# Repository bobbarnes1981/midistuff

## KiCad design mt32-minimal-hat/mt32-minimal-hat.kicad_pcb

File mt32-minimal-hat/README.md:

# mt32 minimal hat

https://github.com/raspberrypi/hats/blob/master/uhat-board-mechanical.pdf

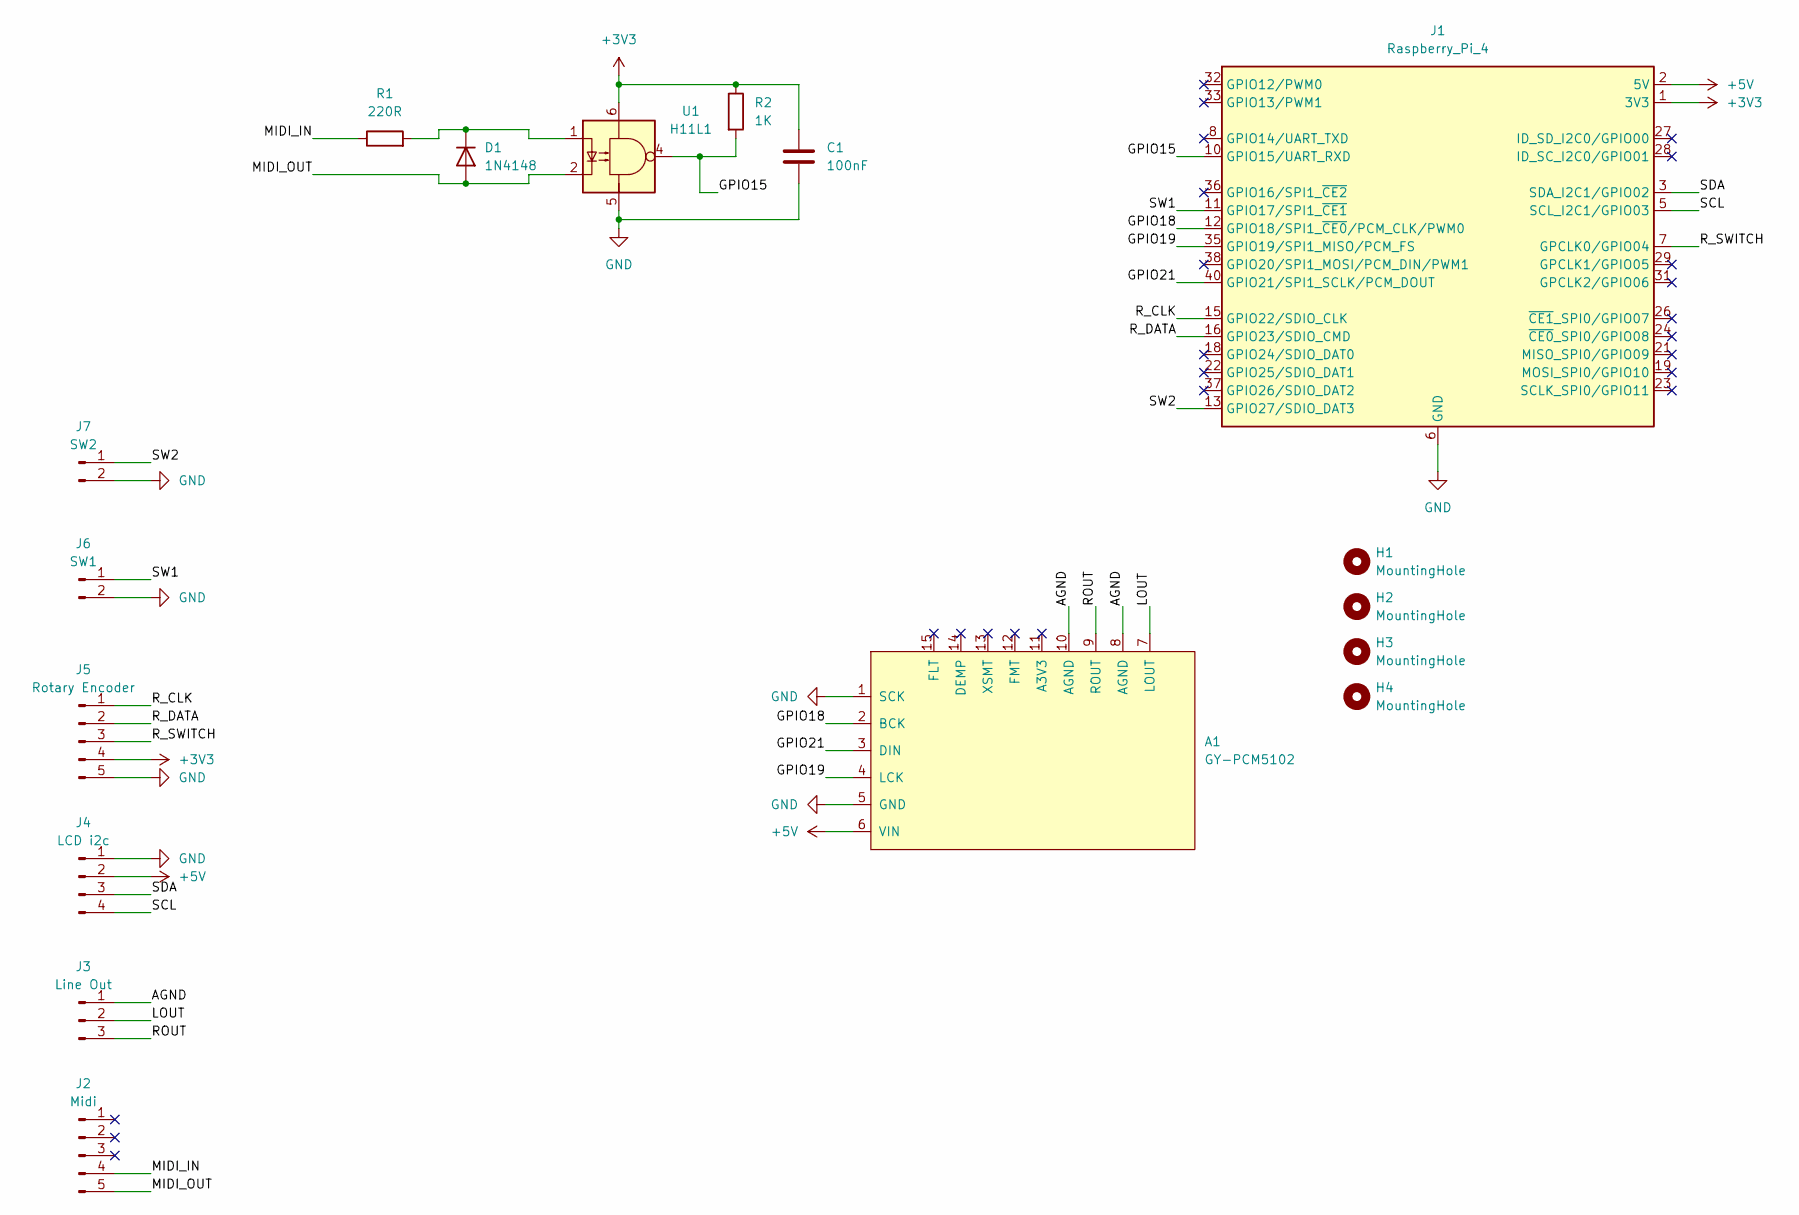
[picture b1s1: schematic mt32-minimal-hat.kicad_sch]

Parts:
A1: GY-PCM5102
C1: 100nF; C_Disc_D5.0mm_W2.5mm_P5.00mm
D1: 1N4148; D_DO-35_SOD27_P7.62mm_Horizontal
H1, H2, H3, H4: MountingHole; MountingHole_2.7mm_M2.5
J1: Raspberry_Pi_4; PinSocket_2x20_P2.54mm_Vertical
J2: Midi; PinHeader_1x05_P2.54mm_Vertical
J3: Line Out; PinHeader_1x03_P2.54mm_Vertical
J4: LCD i2c; PinHeader_1x04_P2.54mm_Vertical
J5: Rotary Encoder; PinHeader_1x05_P2.54mm_Vertical
J6: SW1; PinHeader_1x02_P2.54mm_Vertical
J7: SW2; PinHeader_1x02_P2.54mm_Vertical
R1: 220R; R_Axial_DIN0207_L6.3mm_D2.5mm_P10.16mm_Horizontal
R2: 1K; R_Axial_DIN0207_L6.3mm_D2.5mm_P10.16mm_Horizontal
U1: H11L1; DIP-6_W7.62mm_Socket_LongPads

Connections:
+3V3: C1.1, J1.1 (3V3), J1.17 (3V3), J5.4, R2.1, U1.6
+5V: A1.6 (VIN), J1.2 (5V), J1.4 (5V), J4.2
/AGND: A1.8 (AGND), A1.10 (AGND), J3.1
/GPIO15: J1.10 (GPIO15/UART_RXD), R2.2, U1.4
/GPIO18: A1.2 (BCK), J1.12 (GPIO18/SPI1_~CE0/PCM_CLK/PWM0)
/GPIO19: A1.4 (LCK), J1.35 (GPIO19/SPI1_MISO/PCM_FS)
/GPIO21: A1.3 (DIN), J1.40 (GPIO21/SPI1_SCLK/PCM_DOUT)
/LOUT: A1.7 (LOUT), J3.2
/MIDI_IN: J2.4, R1.1
/MIDI_OUT: D1.2 (A), J2.5, U1.2
/ROUT: A1.9 (ROUT), J3.3
/R_CLK: J1.15 (GPIO22/SDIO_CLK), J5.1
/R_DATA: J1.16 (GPIO23/SDIO_CMD), J5.2
/R_SWITCH: J1.7 (GPCLK0/GPIO04), J5.3
/SCL: J1.5 (SCL_I2C1/GPIO03), J4.4
/SDA: J1.3 (SDA_I2C1/GPIO02), J4.3
/SW1: J1.11 (GPIO17/SPI1_~CE1), J6.1
/SW2: J1.13 (GPIO27/SDIO_DAT3), J7.1
GND: A1.1 (SCK), A1.5 (GND), C1.2, J1.6 (GND), J1.9 (GND), J1.14 (GND), J1.20 (GND), J1.25 (GND), J1.30 (GND), J1.34 (GND), J1.39 (GND), J4.1, J5.5, J6.2, J7.2, U1.5
unnamed: D1.1 (K), R1.2, U1.1

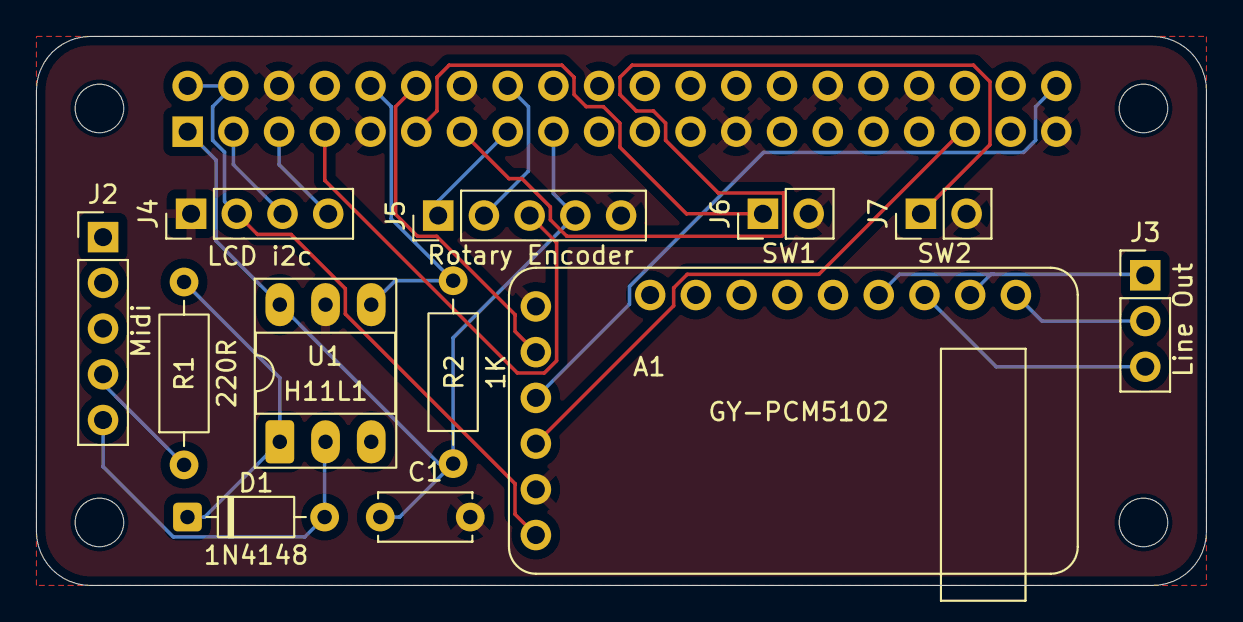
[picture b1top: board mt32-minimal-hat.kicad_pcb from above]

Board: 2 copper layers, 65.0 x 30.5 mm, 17 parts (1 on the bottom side), 20 nets.

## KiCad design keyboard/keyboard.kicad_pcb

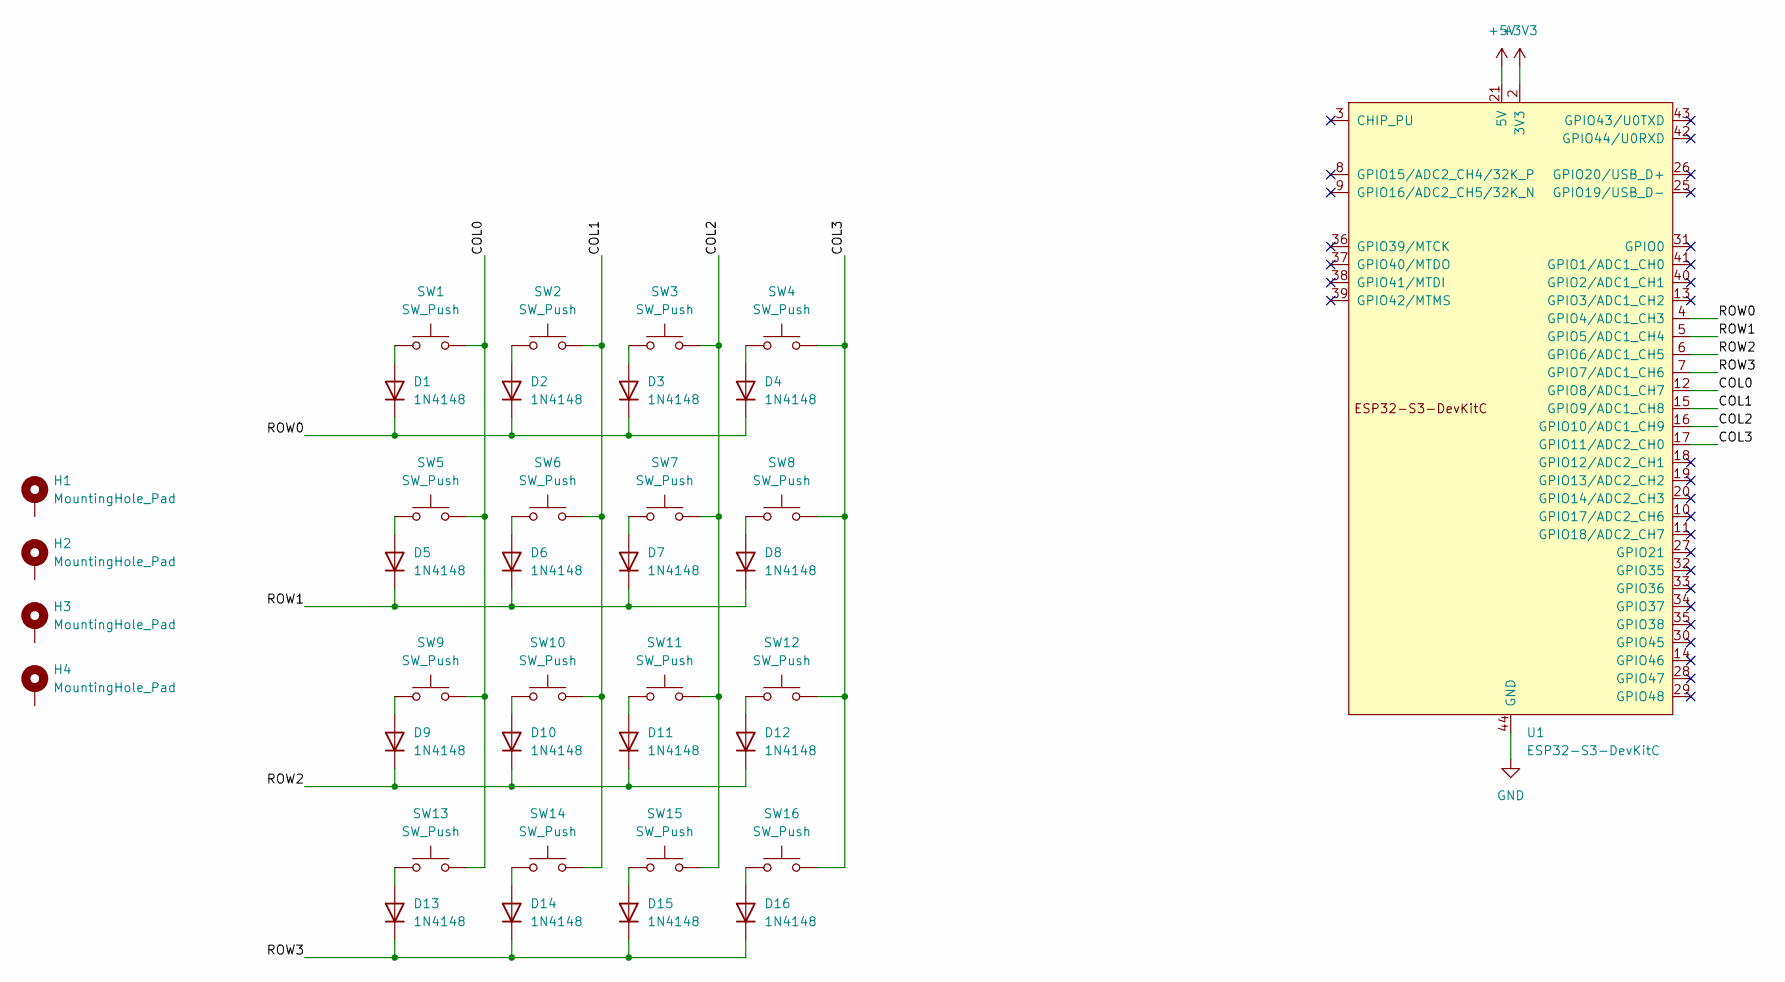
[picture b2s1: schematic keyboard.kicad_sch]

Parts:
D1, D2, D3, D4, D5, D6, D7, D8, D9, D10, D11, D12, D13, D14, D15, D16: 1N4148; D_DO-35_SOD27_P7.62mm_Horizontal
H1, H2, H3, H4: MountingHole_Pad; MountingHole_3.2mm_M3_Pad
SW1, SW2, SW3, SW4, SW5, SW6, SW7, SW8, SW9, SW10, SW11, SW12, SW13, SW14, SW15, SW16: SW_Push; SW_Hotswap_Kailh_MX_1.00u
U1: ESP32-S3-DevKitC

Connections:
+3V3: U1.1 (3V3), U1.2 (3V3)
+5V: U1.21 (5V)
/COL0: SW1.2, SW5.2, SW9.2, SW13.2, U1.12 (GPIO8/ADC1_CH7)
/COL1: SW2.2, SW6.2, SW10.2, SW14.2, U1.15 (GPIO9/ADC1_CH8)
/COL2: SW3.2, SW7.2, SW11.2, SW15.2, U1.16 (GPIO10/ADC1_CH9)
/COL3: SW4.2, SW8.2, SW12.2, SW16.2, U1.17 (GPIO11/ADC2_CH0)
/ROW0: D1.1 (K), D2.1 (K), D3.1 (K), D4.1 (K), U1.4 (GPIO4/ADC1_CH3)
/ROW1: D5.1 (K), D6.1 (K), D7.1 (K), D8.1 (K), U1.5 (GPIO5/ADC1_CH4)
/ROW2: D9.1 (K), D10.1 (K), D11.1 (K), D12.1 (K), U1.6 (GPIO6/ADC1_CH5)
/ROW3: D13.1 (K), D14.1 (K), D15.1 (K), D16.1 (K), U1.7 (GPIO7/ADC1_CH6)
GND: U1.22 (GND), U1.23 (GND), U1.24 (GND), U1.44 (GND)
unnamed: D1.2 (A), SW1.1
unnamed: D2.2 (A), SW2.1
unnamed: D3.2 (A), SW3.1
unnamed: D4.2 (A), SW4.1
unnamed: D5.2 (A), SW5.1
unnamed: D6.2 (A), SW6.1
unnamed: D7.2 (A), SW7.1
unnamed: D8.2 (A), SW8.1
unnamed: D9.2 (A), SW9.1
unnamed: D10.2 (A), SW10.1
unnamed: D11.2 (A), SW11.1
unnamed: D12.2 (A), SW12.1
unnamed: D13.2 (A), SW13.1
unnamed: D14.2 (A), SW14.1
unnamed: D15.2 (A), SW15.1
unnamed: D16.2 (A), SW16.1

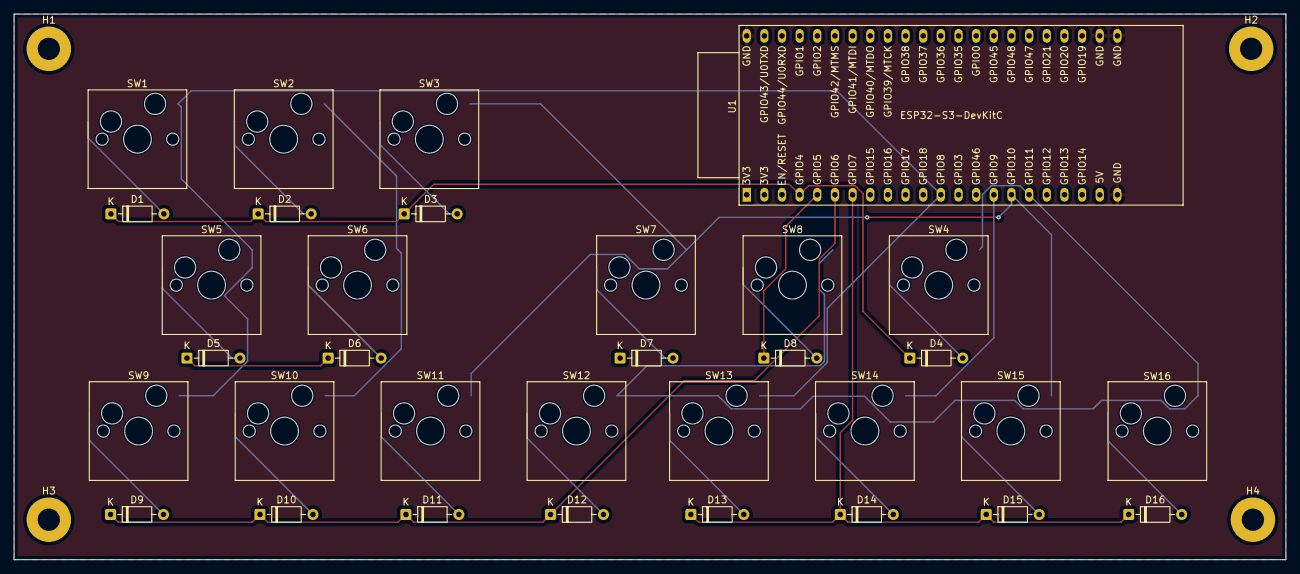
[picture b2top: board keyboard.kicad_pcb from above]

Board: 2 copper layers, 183.0 x 78.5 mm, 37 parts (0 on the bottom side), 26 nets.
